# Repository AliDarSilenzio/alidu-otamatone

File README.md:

# Alidu Otamatone

**Progetto di Dario Amabile** — strumento elettronico a fiato, open source.

L'Otamatone diventato strumento vero: un dito che scivola sul manico sceglie la
nota senza scalini, il fiato in un bocchino dà la dinamica, sei pulsanti cambiano
ottava e suono. Esce in MIDI, su USB e su presa DIN, e comanda qualsiasi
sintetizzatore. Il cervello è un Teensy 4.1.

Progettato per **non avere parti che si consumano**: le note si leggono con un
nastro capacitivo sotto una lastra protettiva, senza contatto.

🌐 **Sito del progetto**: cartella `docs/` (pubblicabile con GitHub Pages).

## Contenuto

| Cartella / file | Che cosa c'è |
|---|---|
| `docs/` | Il sito: presentazione, confronto con l'Otamatone, prova nel browser, download |
| `firmware/AliBreath/AliBreath.ino` | Firmware per Teensy 4.1 (Arduino / Teensyduino) |
| `hardware/nastro/` | Circuito stampato del nastro delle note (60 elettrodi in due metà uguali) |
| `hardware/scheda/` | Circuito stampato della scheda principale |
| `hardware/meccanica/` | Pezzi stampabili in 3D: sorgente OpenSCAD, 7 file STL, immagini |
| `hardware/produci.sh` | Rigenera i circuiti, li verifica (DRC) e prepara Gerber e immagini |
| `docs/costruzione.html` | Guida di costruzione completa |
| `AliBreath.kicad_sch`, `.kicad_sym`, `.kicad_pro` | Schema elettrico KiCad, revisione 4 |
| `genera_kicad.py` | Genera lo schema da codice: cambi un valore e rigeneri |
| `AliBreath_schema.pdf` | Schema in PDF |
| `SCHEMA_ELETTRICO.md` | Componenti, nodi, calcoli, regole di montaggio |
| `licenze/` | Testi completi delle licenze |

## Caricare il firmware

1. Installa Arduino IDE e Teensyduino.
2. Dal Gestore librerie installa **Trill** (Bela).
3. Apri `firmware/AliBreath/AliBreath.ino`.
4. Scheda: **Teensy 4.1** · USB Type: **MIDI**.
5. Carica. All'accensione non toccare il nastro e non soffiare per un secondo:
   lo strumento si tara.

Da riga di comando:

```
arduino-cli compile --fqbn teensy:avr:teensy41:usb=midi firmware/AliBreath
```

## Stato

- ✅ Schema elettrico rev. 4, ERC KiCad senza errori
- ✅ Firmware: compila per Teensy 4.1
- ⏳ Firmware: da provare sullo strumento, soglie da tarare al banco
- ✅ Circuiti stampati del nastro e della scheda principale: DRC KiCad 0 errori, 0 collegamenti mancanti
- ✅ Guida di costruzione
- ⏳ Circuiti da produrre e montare
- ✅ Meccanica stampabile (OpenSCAD → 7 STL)
- ⏳ Stampa, montaggio e primo prototipo

Foto e video nel sito sono immagini concettuali generate al computer: il
prototipo fisico non è ancora stato costruito.

## Licenze

- **Hardware** (schemi, file KiCad): CERN-OHL-S v2 — `licenze/CERN-OHL-S-2.0.txt`
- **Firmware**: GNU GPL v3 — `licenze/GPL-3.0.txt`
- **Testi, immagini, video**: CC BY-SA 4.0 — `licenze/CC-BY-SA-4.0.txt`

La libreria Trill usata dal firmware è di Augmented Instruments Ltd (Bela), con
licenza BSD.

"Otamatone" è un marchio dei rispettivi proprietari; questo progetto è
indipendente e non è affiliato con loro.

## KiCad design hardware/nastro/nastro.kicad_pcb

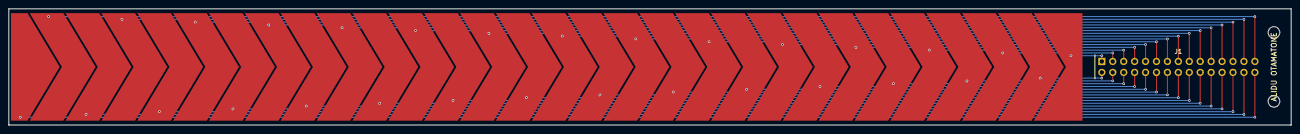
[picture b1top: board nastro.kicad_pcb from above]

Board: 2 copper layers, 298.0 x 27.0 mm, 33 parts (0 on the bottom side), 30 nets.

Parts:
E00, E01, E02, E03, E04, E05, E06, E07, E08, E09, E10, E11, E12, E13, E14, E15, E16, E17, E18, E19, E20, E21, E22, E23, E24, E25, E26, E27, E28, E29: Elettrodo
H1, H2: M2.5; Foro_M2.5
J1: 2x15 2,54 mm; Connettore_2x15_P2.54

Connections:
CH00: E00.1, J1.1
CH01: E01.1, J1.2
CH02: E02.1, J1.3
CH03: E03.1, J1.4
CH04: E04.1, J1.5
CH05: E05.1, J1.6
CH06: E06.1, J1.7
CH07: E07.1, J1.8
CH08: E08.1, J1.9
CH09: E09.1, J1.10
CH10: E10.1, J1.11
CH11: E11.1, J1.12
CH12: E12.1, J1.13
CH13: E13.1, J1.14
CH14: E14.1, J1.15
CH15: E15.1, J1.16
CH16: E16.1, J1.17
CH17: E17.1, J1.18
CH18: E18.1, J1.19
CH19: E19.1, J1.20
CH20: E20.1, J1.21
CH21: E21.1, J1.22
CH22: E22.1, J1.23
CH23: E23.1, J1.24
CH24: E24.1, J1.25
CH25: E25.1, J1.26
CH26: E26.1, J1.27
CH27: E27.1, J1.28
CH28: E28.1, J1.29
CH29: E29.1, J1.30

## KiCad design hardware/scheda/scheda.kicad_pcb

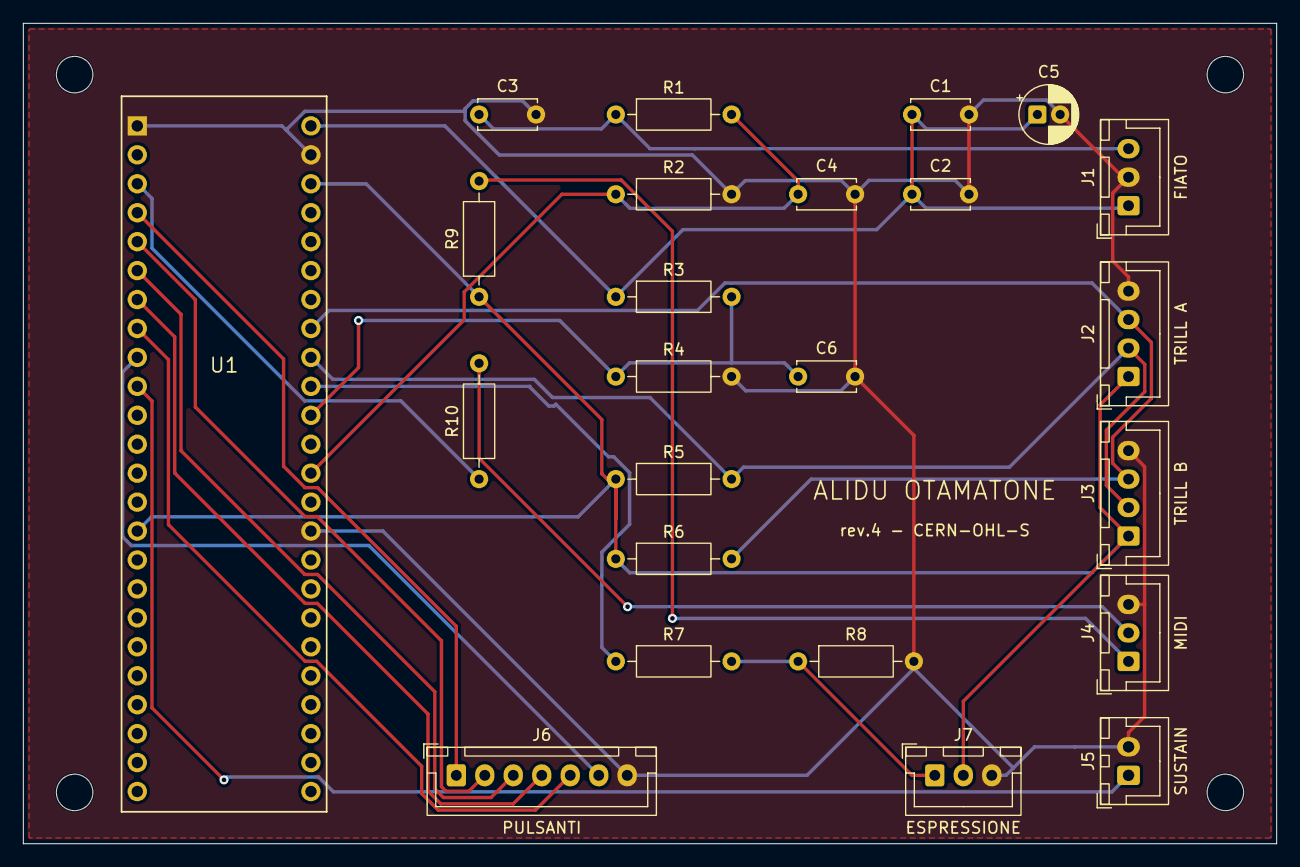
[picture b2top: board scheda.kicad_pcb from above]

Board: 2 copper layers, 110.0 x 72.0 mm, 28 parts (0 on the bottom side), 20 nets.

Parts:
C1, C4, C6: 100n; C_Disc_D5.0mm_W2.5mm_P5.00mm
C2: 1u; C_Disc_D5.0mm_W2.5mm_P5.00mm
C3: 1n; C_Disc_D5.0mm_W2.5mm_P5.00mm
C5: 10u; CP_Radial_D5.0mm_P2.00mm
H1, H2, H3, H4: MountingHole_3.2mm_M3
J1: FIATO; JST_XH_B3B-XH-A_1x03_P2.50mm_Vertical
J2: TRILL A; JST_XH_B4B-XH-A_1x04_P2.50mm_Vertical
J3: TRILL B; JST_XH_B4B-XH-A_1x04_P2.50mm_Vertical
J4: MIDI; JST_XH_B3B-XH-A_1x03_P2.50mm_Vertical
J5: SUSTAIN; JST_XH_B2B-XH-A_1x02_P2.50mm_Vertical
J6: PULSANTI; JST_XH_B7B-XH-A_1x07_P2.50mm_Vertical
J7: ESPRESSIONE; JST_XH_B3B-XH-A_1x03_P2.50mm_Vertical
R1, R3, R5, R6: 4k7; R_Axial_DIN0207_L6.3mm_D2.5mm_P10.16mm_Horizontal
R2, R4: 12k; R_Axial_DIN0207_L6.3mm_D2.5mm_P10.16mm_Horizontal
R7: 1k; R_Axial_DIN0207_L6.3mm_D2.5mm_P10.16mm_Horizontal
R8: 100k; R_Axial_DIN0207_L6.3mm_D2.5mm_P10.16mm_Horizontal
R9: 33; R_Axial_DIN0207_L6.3mm_D2.5mm_P10.16mm_Horizontal
R10: 10; R_Axial_DIN0207_L6.3mm_D2.5mm_P10.16mm_Horizontal
U1: Teensy 4.1; Teensy_4.1

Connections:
+3V3: J2.1, J3.1, J7.2, R5.1, R6.1, R9.1, U1.3V3
+5V: C1.1, C2.1, C5.1, J1.1, R3.1, U1.VIN
GND: C1.2, C2.2, C3.2, C4.2, C5.2, C6.2, J1.2, J2.4, J3.4, J4.3, J5.2, J6.7, J7.3, R2.2, R4.2, R8.2, U1.GND
unnamed: J4.1, R9.2
unnamed: J4.2, R10.2
unnamed: J5.1, U1.8
unnamed: J7.1, R7.2, R8.1
unnamed: C4.1, R1.2, R2.1, U1.14
unnamed: C6.1, R3.2, R4.1, U1.16
unnamed: R7.1, U1.17
unnamed: J6.1, U1.2
unnamed: J6.2, U1.3
unnamed: J6.3, U1.4
unnamed: J6.4, U1.5
unnamed: J6.5, U1.6
unnamed: J6.6, U1.7
unnamed: J2.3, J3.3, R6.2, U1.19
unnamed: J2.2, J3.2, R5.2, U1.18
unnamed: R10.1, U1.1
unnamed: C3.1, J1.3, R1.1

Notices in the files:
hardware/nastro/nastro.kicad_pcb:
NASTRO 1/2 - CC BY-SA / CERN-OHL-S
hardware/scheda/scheda.kicad_pcb:
rev.4 - CERN-OHL-S
